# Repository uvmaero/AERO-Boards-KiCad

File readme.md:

# Readme

This repo was originally @willemcvu 's personal AERO boards repo. From 2019-20 onward it will be used by all of AERO to store boards designed for the AERO cars.

Some are finished and have been produced, tested, etc. Others have not. Up to you to figure out if a particular board might be useful for your needs.

If you do produce a board, let me know! I'd love to know what you're using it for.

Everything here is licensed under CC-BY-SA and thus is OSHWA-compliant.

# The Boards

(Often out-of-date) descriptions of what these boards do.

## BattMon

Monitors the current/voltage to/from a battery and power consumer. Includes a relay on the battery, ATMega328p, and CANBUS interface. This board has been produced and partially tested.

## CANShield
A generic Arduino Uno CANBUS shield. Once hooked up to an Uno, it is the same circuit used for all the boards with CANBUS+ATMega328p found here. Untested and unproduced.

## DC_DCBoard - Superseded by interface-board ("BigBoi")
Converts ~300VDC to ~12VDC using a DCM CHiP module from Vicor Power. Can do 400W peak, will dissapate almost 40W at that load, so it has a 19mm Vicor heatsink, model #(?can't remember).  Version 1 has clearance issues. Version 2 is an intermediate version with those issues mostly fixed. Version 3 is still be designed, and it will be the final version. None have been produced or tested, and all probably have issues (v1 and v2 have known issues, and v3 isn't finished).

## FanBoy - Superseded by interface-board ("BigBoi")
Simple 4-channel PWM fan controller with ATMega328p and CANBUS interface. Tested, works great. Should be able to do ~15A a channel, although this hasn't been tested, and is probably not recommended.

## interface-board (aka "BigBoi")
Contains all the high-voltage interface circuitry. Hosts a Vicor DC/DC converter module that generates 12V for the entire car. Also controls fans, pump, and brakelight, and includes CANBUS interface, NTC inputs, and some assorted other functionality. "standoffs-biggerbox" is the current working version. Competition-tested, working 100%.

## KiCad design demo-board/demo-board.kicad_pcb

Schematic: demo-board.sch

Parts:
C1: 0.1U; C_0603_1608Metric_Pad1.05x0.95mm_HandSolder
C2: 10U; C_0603_1608Metric_Pad1.05x0.95mm_HandSolder
D1, D2, D3, D4, D5, D6, D7, D8: WS2812B; LED_WS2812B_PLCC4_5.0x5.0mm_P3.2mm
J1: USB_B_Micro; USB_Micro-B_Molex-105017-0001
J2: Conn_02x03_Odd_Even; PinHeader_2x03_P2.54mm_Vertical
JP1, JP2, JP3, JP4, JP5, JP6, JP7, JP8: Jumper_2_Open; SolderJumper-2_P1.3mm_Open_RoundedPad1.0x1.5mm
R1: 1OK; R_0603_1608Metric_Pad1.05x0.95mm_HandSolder
U1: ATtiny85-20SU; SOIJ-8_5.3x5.3mm_P1.27mm

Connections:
+5V: C1.1, C2.1, D1.1 (VDD), D2.1 (VDD), D3.1 (VDD), D4.1 (VDD), D5.1 (VDD), D6.1 (VDD), D7.1 (VDD), D8.1 (VDD), J1.1 (VBUS), J2.2, R1.1, U1.8 (VCC)
/MISO: J2.1, U1.6 (PB1)
/MOSI: J2.4, U1.5 (AREF/PB0)
/RST: J2.5, R1.2, U1.1 (~RESET~/PB5)
/SCK: J2.3, U1.7 (PB2)
GND: C1.2, C2.2, D1.3 (VSS), D2.3 (VSS), D3.3 (VSS), D4.3 (VSS), D5.3 (VSS), D6.3 (VSS), D7.3 (VSS), D8.3 (VSS), J1.5 (GND), J1.6 (Shield), J2.6, U1.4 (GND)
unnamed: D1.2 (DOUT), D3.4 (DIN), JP1.2 (B), JP3.1 (A)
unnamed: D1.4 (DIN), JP1.1 (A), U1.2 (XTAL1/PB3)
unnamed: D2.2 (DOUT), D4.4 (DIN), JP2.2 (B), JP4.1 (A)
unnamed: D2.4 (DIN), D7.2 (DOUT), JP2.1 (A), JP7.2 (B)
unnamed: D3.2 (DOUT), D5.4 (DIN), JP3.2 (B), JP5.1 (A)
unnamed: D4.2 (DOUT), D6.4 (DIN), JP4.2 (B), JP6.1 (A)
unnamed: D5.2 (DOUT), D7.4 (DIN), JP5.2 (B), JP7.1 (A)
unnamed: D6.2 (DOUT), D8.4 (DIN), JP6.2 (B), JP8.1 (A)
unnamed: D8.2 (DOUT), JP8.2 (B)

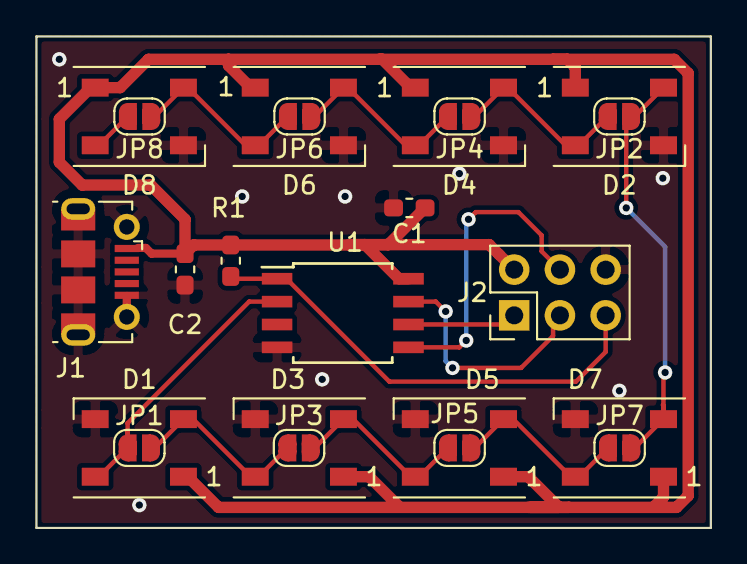
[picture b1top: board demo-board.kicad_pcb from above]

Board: 2 copper layers, 37.5 x 27.3 mm, 22 parts (0 on the bottom side), 15 nets.

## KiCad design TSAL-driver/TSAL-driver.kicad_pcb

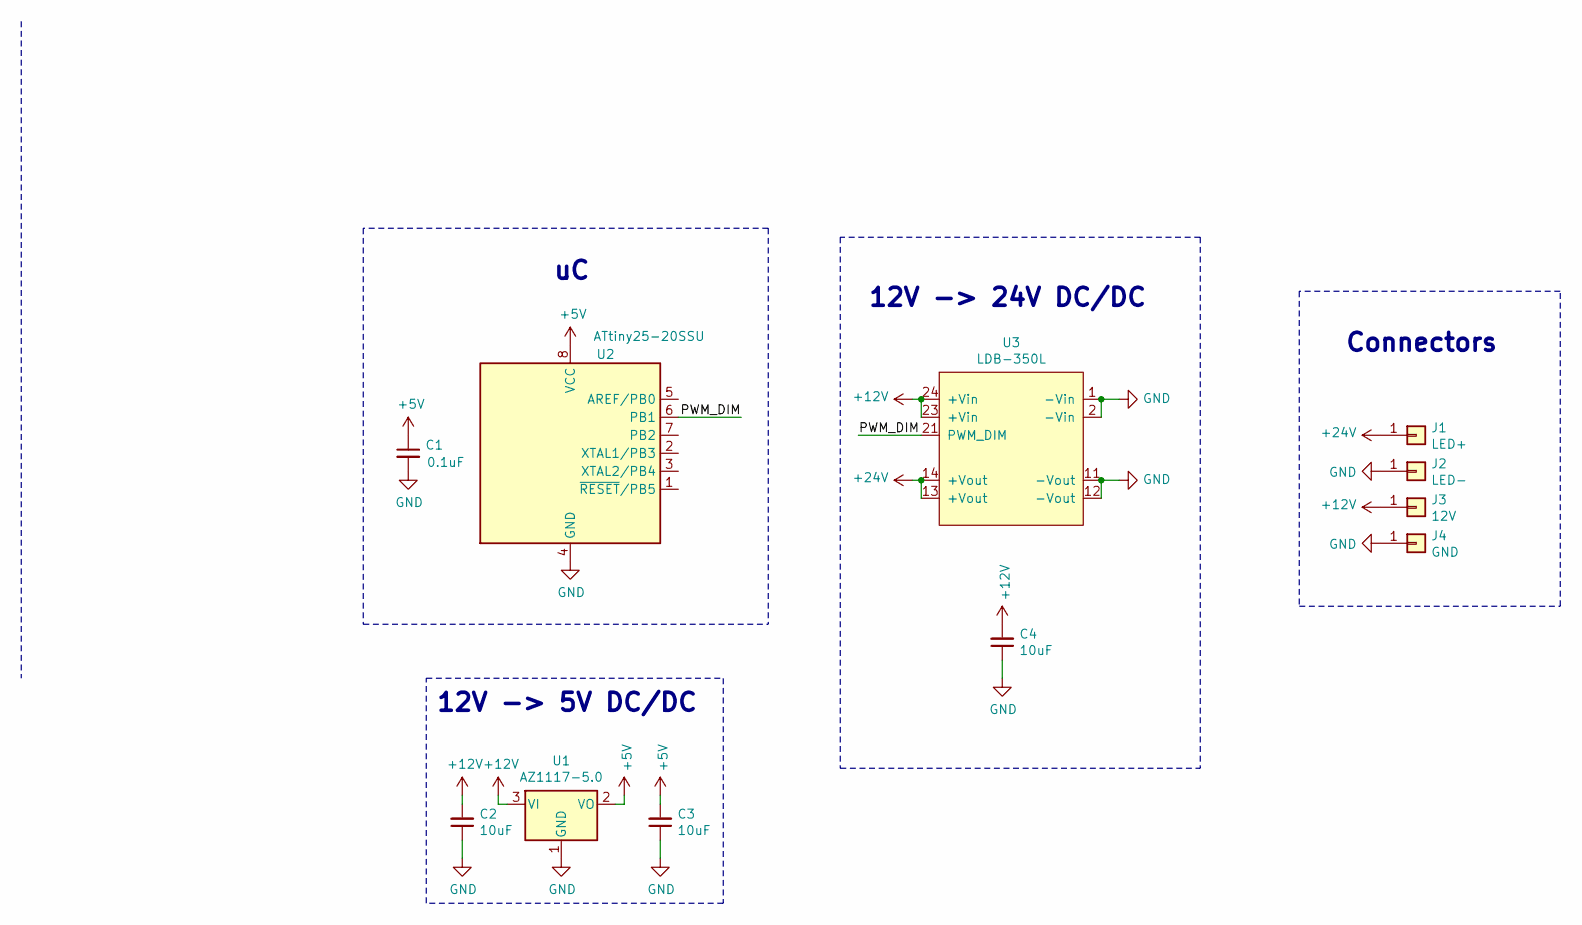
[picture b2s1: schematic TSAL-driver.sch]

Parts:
C1: 0.1uF; C_0603_1608Metric
C2, C3, C4: 10uF; C_0603_1608Metric
J1: LED+; TE_1217861-1
J2: LED-; TE_1217861-1
J3: 12V; TE_1217861-1
J4: GND; TE_1217861-1
U1: AZ1117-5.0; SOT-223-3_TabPin2
U2: ATtiny25-20SSU; SOIC-8_3.9x4.9mm_P1.27mm
U3: LDB-350L; LDB-_L

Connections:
+5V: C1.1, C3.2, U1.2 (VO), U2.8 (VCC)
+12V: C2.2, C4.2, J3.1, U1.3 (VI), U3.23 (+Vin), U3.24 (+Vin)
+24V: J1.1, U3.13 (+Vout), U3.14 (+Vout)
/PWM_DIM: U2.6 (PB1), U3.21 (PWM_DIM)
GND: C1.2, C2.1, C3.1, C4.1, J2.1, J4.1, U1.1 (GND), U2.4 (GND), U3.1 (-Vin), U3.2 (-Vin), U3.11 (-Vout), U3.12 (-Vout)

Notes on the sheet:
12V -> 24V DC/DC
Connectors
12V -> 5V DC/DC

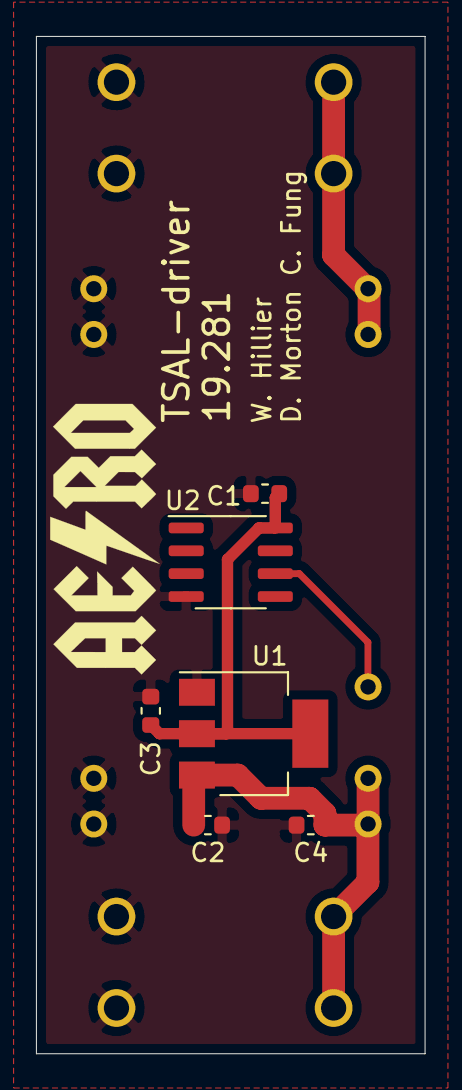
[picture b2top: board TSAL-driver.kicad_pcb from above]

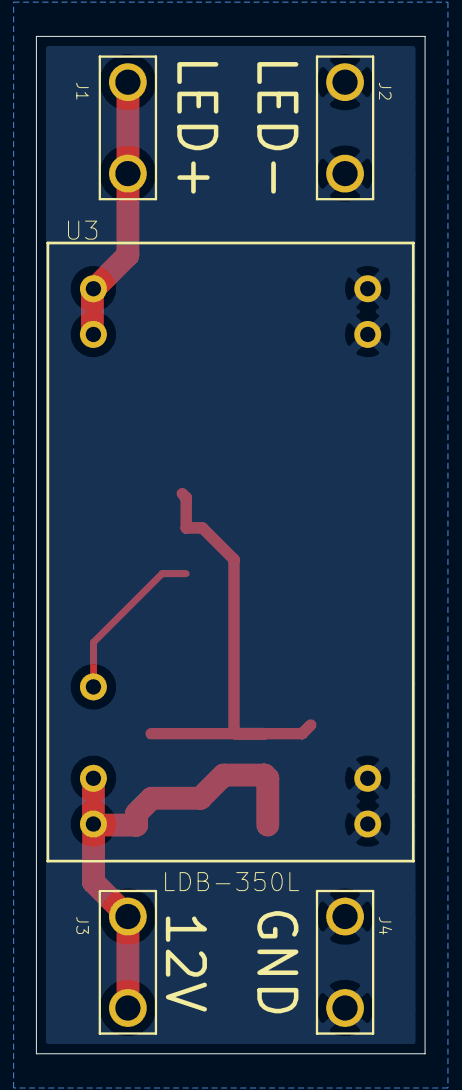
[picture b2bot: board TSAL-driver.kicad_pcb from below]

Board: 2 copper layers, 21.6 x 56.5 mm, 11 parts (5 on the bottom side), 5 nets.

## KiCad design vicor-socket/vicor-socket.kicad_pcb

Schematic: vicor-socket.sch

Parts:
J1: Interface; PinHeader_1x03_P2.54mm_Vertical
J2: HV+; MountingHole_3.2mm_M3_Pad_Via
J3: HV-; MountingHole_3.2mm_M3_Pad_Via
J4: 12V+; MountingHole_3.2mm_M3_Pad_Via
J5: 12V-; MountingHole_3.2mm_M3_Pad_Via
U1: DCM4623TD2J13D0T70-AEROParts; DCM4623TD2J13D0T70_w_landpattern

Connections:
unnamed: J1.1, U1.4 (FT)
unnamed: J1.2, U1.3 (EN)
unnamed: J1.3, U1.2 (TR)
unnamed: J2.1, U1.1 (+IN)
unnamed: J3.1, U1.5 (-IN)
unnamed: J4.1, U1.7 (+OUT), U1.9 (+OUT)
unnamed: J5.1, U1.6 (-OUT), U1.8 (-OUT)

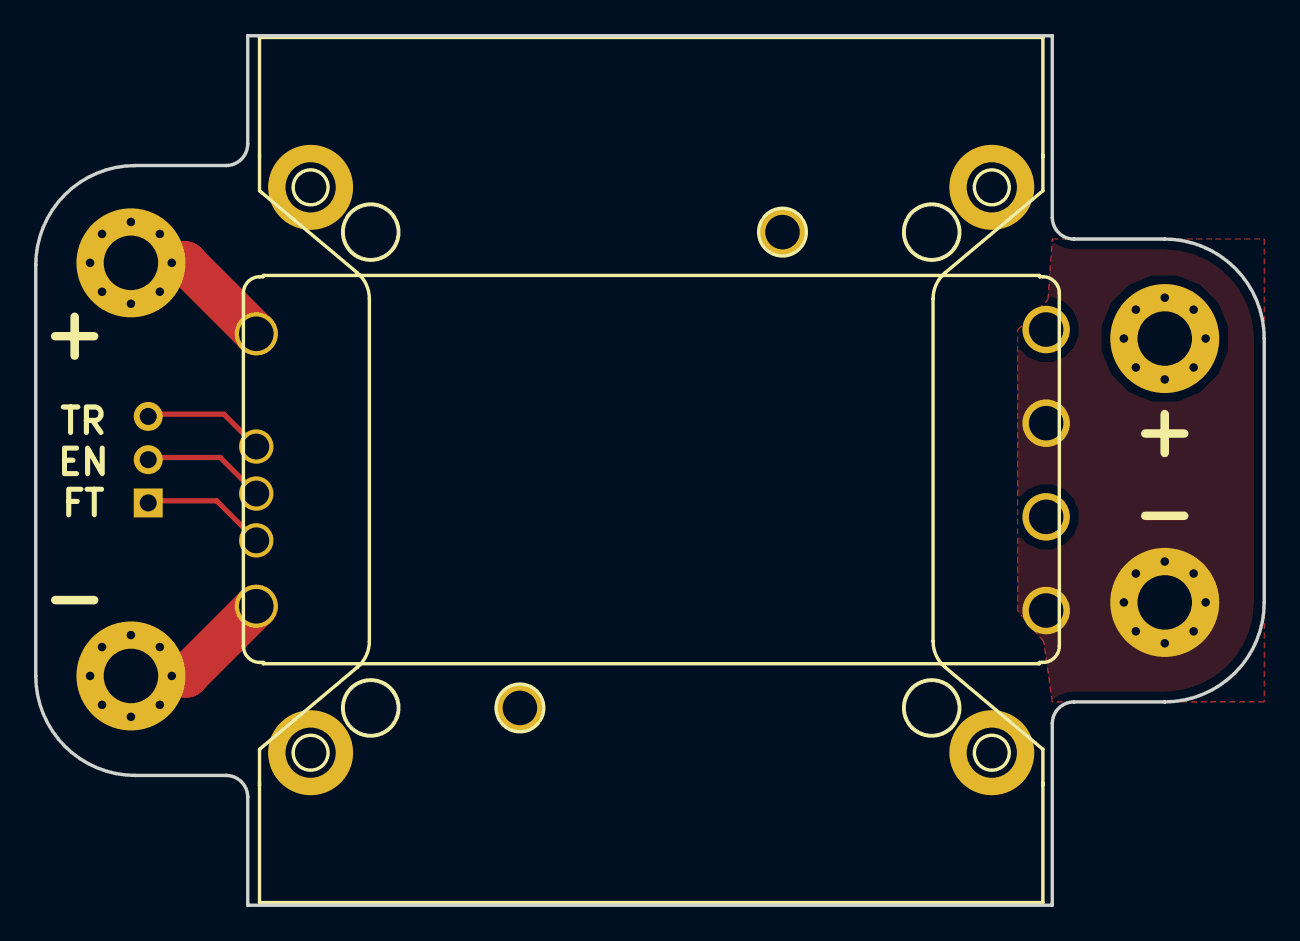
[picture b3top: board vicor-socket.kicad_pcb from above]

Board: 2 copper layers, 72.1 x 51.1 mm, 6 parts (1 on the bottom side), 7 nets.

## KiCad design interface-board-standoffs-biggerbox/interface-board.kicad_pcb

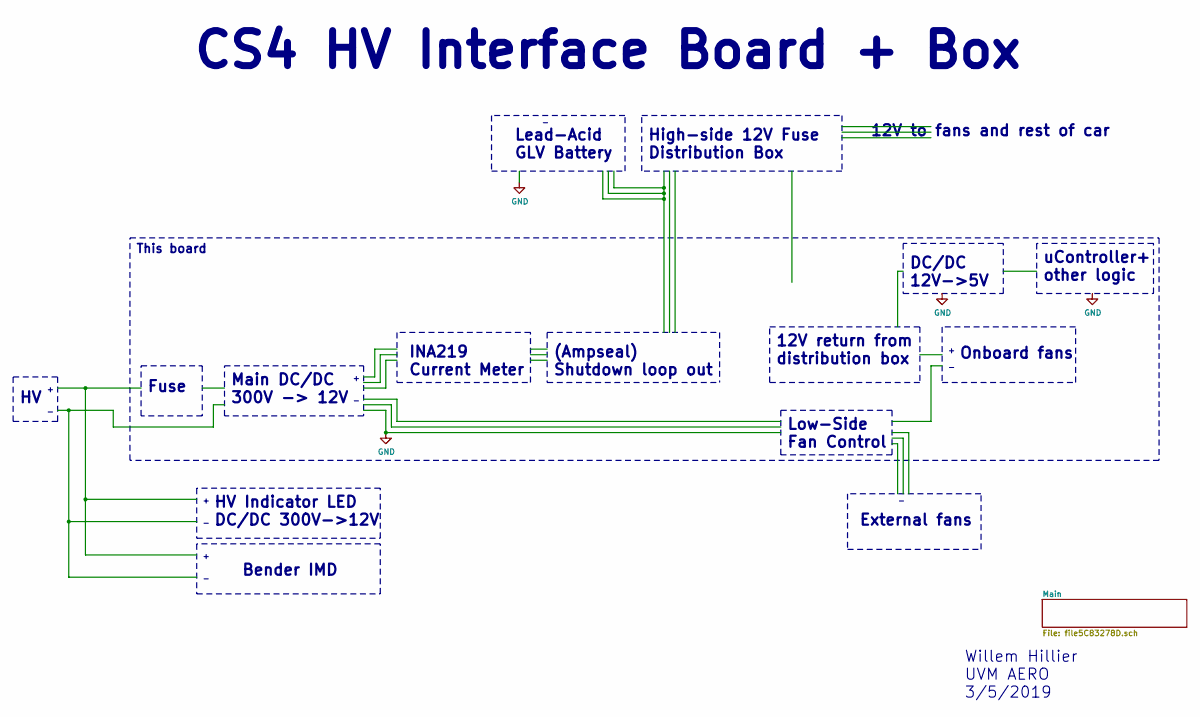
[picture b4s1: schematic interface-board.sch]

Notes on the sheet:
CS4 HV Interface Board + Box
Main DC/DC 300V -> 12V
HV Indicator LED DC/DC 300V->12V
INA219 Current Meter
(Ampseal) Shutdown loop out
Fuse
DC/DC 12V->5V
Low-Side Fan Control
High-side 12V Fuse Distribution Box
12V return from distribution box
uController+ other logic
Onboard fans
This board
External fans
12V to fans and rest of car
Willem Hillier UVM AERO 3/5/2019
Bender IMD
Lead-Acid GLV Battery

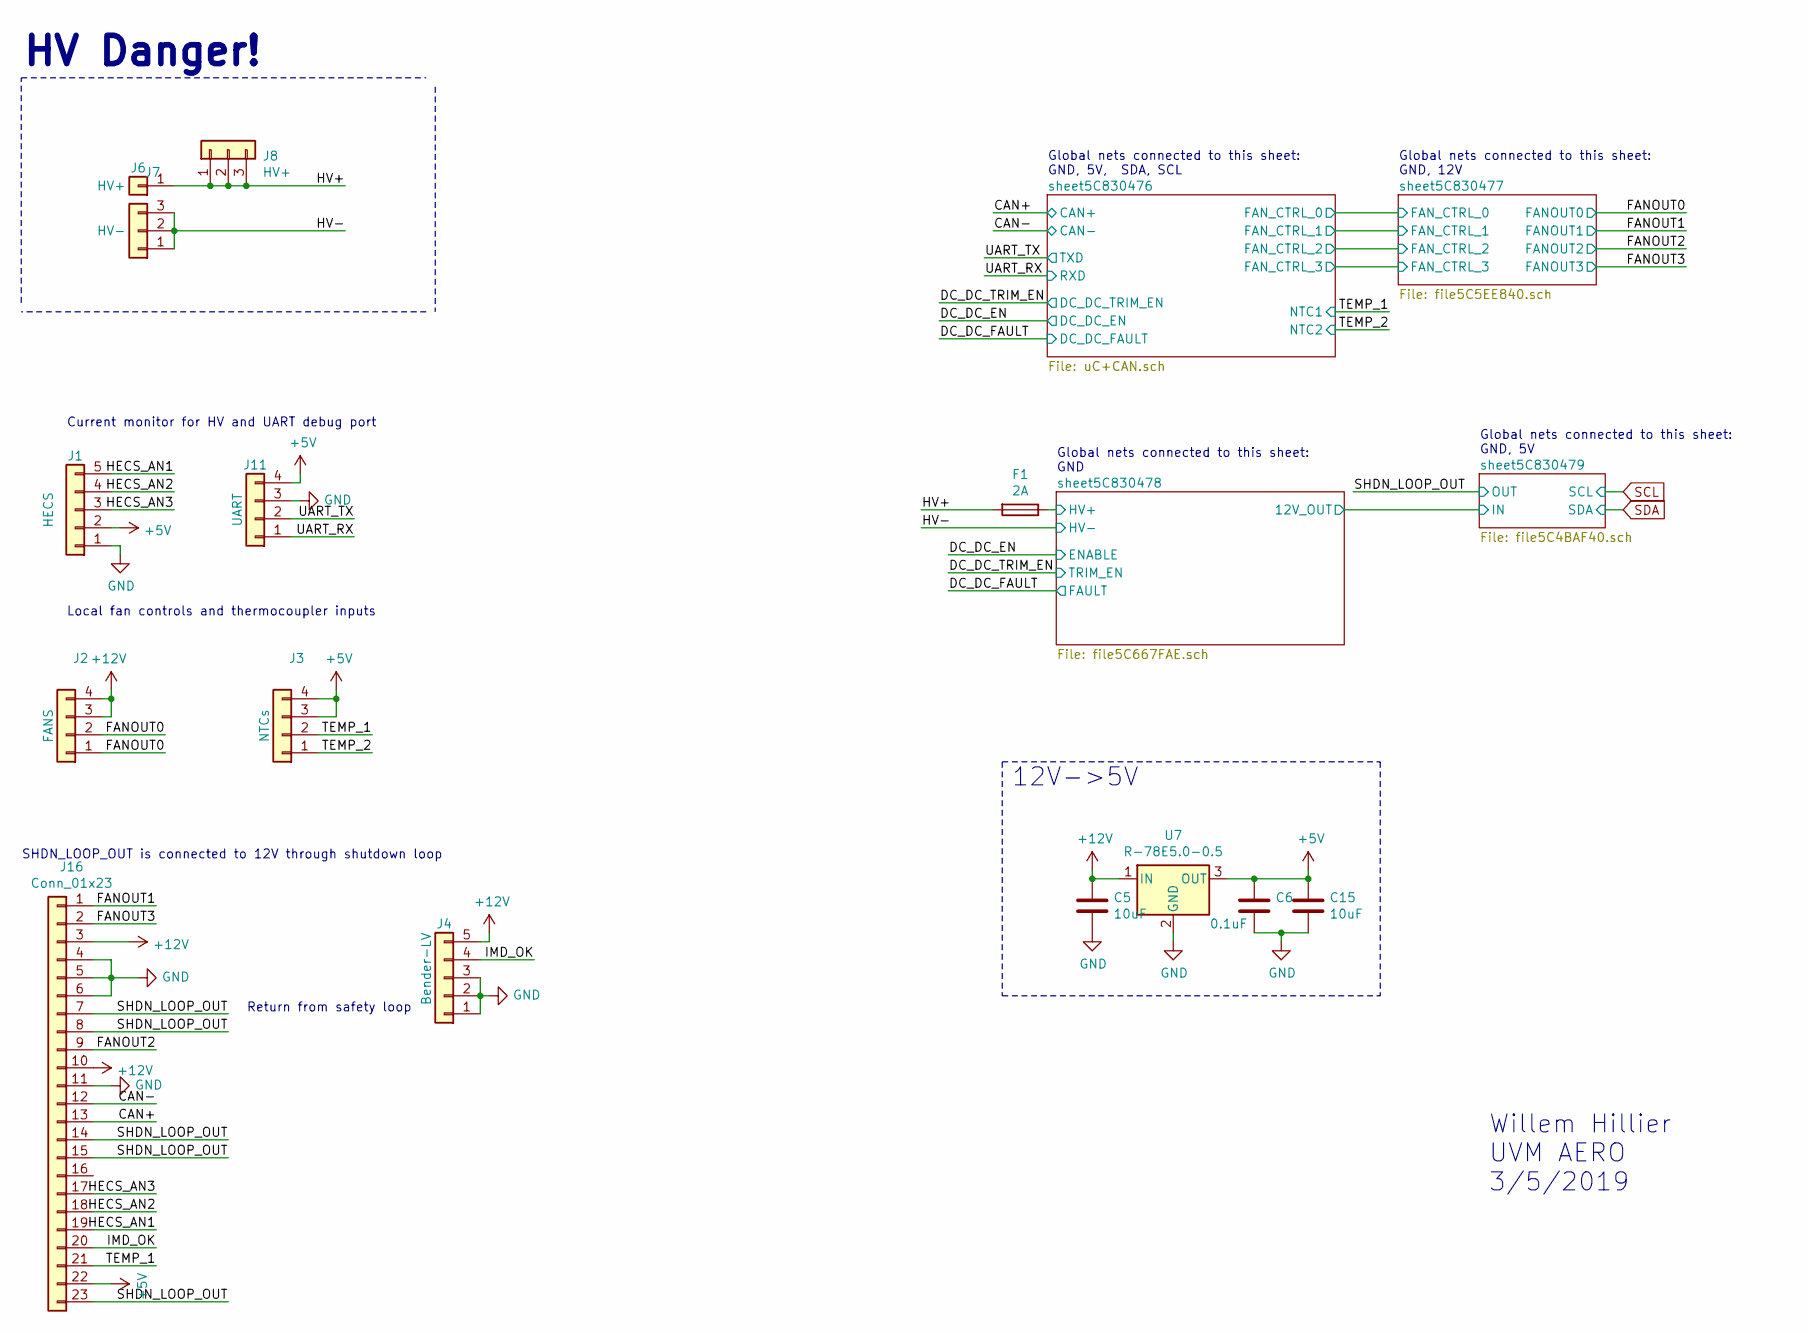
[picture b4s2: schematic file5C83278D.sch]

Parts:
C5, C15: 10uF; C_0603_1608Metric
C6: 0.1uF; C_0603_1608Metric
F1: 2A; Fuseholder_Cylinder-5x20mm_Schurter_0031_8201_Horizontal_Op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
J1: HECS; Molex_KK-254_AE-6410-05A_1x05_P2.54mm_Vertical
J2: FANS; JST_PH_B4B-PH-K_1x04_P2.00mm_Vertical
J3: NTCs; JST_PH_B4B-PH-K_1x04_P2.00mm_Vertical
J4: Bender-LV; Molex_KK-254_AE-6410-05A_1x05_P2.54mm_Vertical
J6: HV+; MountingHole_4.3mm_M4_Pad_Via
J7: HV-; TE_MATE-N-LOK_1-770870-x_1x03_P4.14mm_Vertical
J8: HV+; TE_MATE-N-LOK_1-770870-x_1x03_P4.14mm_Vertical
J11: UART; PinSocket_1x04_P2.54mm_Vertical
J16: Conn_01x23; TE_1-776087-1
U7: R-78E5.0-0.5; Converter_DCDC_RECOM_R-78E-0.5_THT

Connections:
+5V: C6.1, C15.1, J1.2, J3.3, J3.4, J11.4, J16.22, U7.3 (OUT); also elsewhere on the board
+12V: C5.1, J2.3, J2.4, J4.5, J16.3, J16.10, U7.1 (IN); also elsewhere on the board
/Main/CAN+: J16.13; also elsewhere on the board
/Main/CAN-: J16.12; also elsewhere on the board
/Main/FANOUT0: J2.1, J2.2; also elsewhere on the board
/Main/FANOUT1: J16.1; also elsewhere on the board
/Main/FANOUT2: J16.9; also elsewhere on the board
/Main/FANOUT3: J16.2; also elsewhere on the board
/Main/HECS_AN1: J1.5, J16.19
/Main/HECS_AN2: J1.4, J16.18
/Main/HECS_AN3: J1.3, J16.17
/Main/HV+: F1.2, J6.1, J8.1, J8.2, J8.3
/Main/HV-: J7.1, J7.2, J7.3; also elsewhere on the board
/Main/IMD_OK: J4.4, J16.20
/Main/SHDN_LOOP_OUT: J16.7, J16.8, J16.14, J16.15, J16.23; also elsewhere on the board
/Main/TEMP_1: J3.2, J16.21; also elsewhere on the board
/Main/TEMP_2: J3.1; also elsewhere on the board
/Main/UART_RX: J11.1; also elsewhere on the board
/Main/UART_TX: J11.2; also elsewhere on the board
/Main/sheet5C830478/HV+: F1.1; also elsewhere on the board
GND: C5.2, C6.2, C15.2, J1.1, J4.1, J4.2, J4.3, J11.3, J16.4, J16.5, J16.6, J16.11, U7.2 (GND); also elsewhere on the board

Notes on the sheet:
Global nets connected to this sheet: GND, 5V, SDA, SCL
Global nets connected to this sheet: GND, 12V
Global nets connected to this sheet: GND
Global nets connected to this sheet: GND, 5V
HV Danger!
Return from safety loop
SHDN_LOOP_OUT is connected to 12V through shutdown loop
Local fan controls and thermocoupler inputs
Current monitor for HV and UART debug port
12V->5V
Willem Hillier UVM AERO 3/5/2019

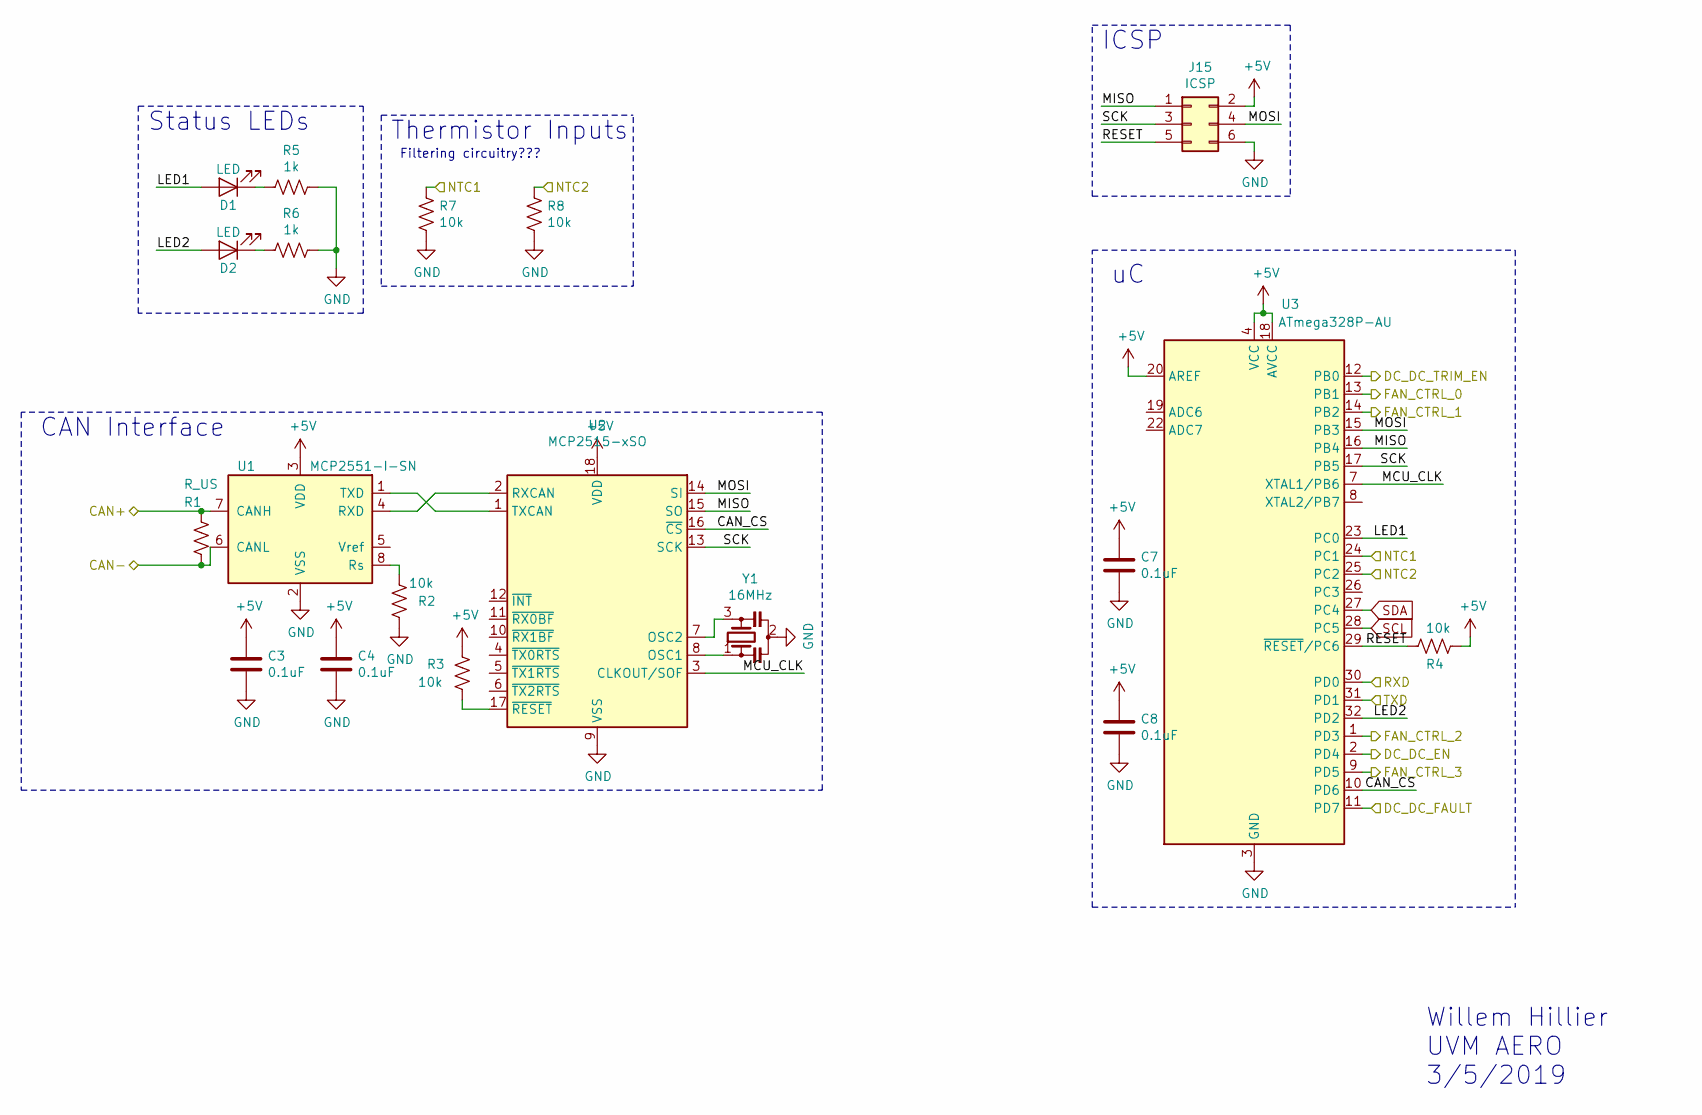
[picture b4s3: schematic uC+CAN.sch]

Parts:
C3, C4, C7, C8: 0.1uF; C_0603_1608Metric
D1, D2: LED; LED_0603_1608Metric
J15: ICSP; PinSocket_2x03_P2.54mm_Vertical
R1: R_US; R_0603_1608Metric
R2, R3, R4, R7, R8: 10k; R_0603_1608Metric
R5, R6: 1k; R_0603_1608Metric
U1: MCP2551-I-SN; SOIC-8_3.9x4.9mm_P1.27mm
U2: MCP2515-xSO; SOIC-18W_7.5x11.6mm_P1.27mm
U3: ATmega328P-AU; TQFP-32_7x7mm_P0.8mm
Y1: 16MHz; Resonator_SMD_muRata_CSTxExxV-3Pin_3.0x1.1mm

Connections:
+5V: C3.1, C4.1, C7.1, C8.1, J15.2, R3.1, R4.1, U1.3 (VDD), U2.18 (VDD), U3.4 (VCC), U3.6 (VCC), U3.18 (AVCC), U3.20 (AREF); also elsewhere on the board
/Main/CAN+: R1.1, U1.7 (CANH); also elsewhere on the board
/Main/CAN-: R1.2, U1.6 (CANL); also elsewhere on the board
/Main/DC_DC_EN: U3.2 (PD4); also elsewhere on the board
/Main/DC_DC_FAULT: U3.11 (PD7); also elsewhere on the board
/Main/TEMP_1: R7.2, U3.24 (PC1); also elsewhere on the board
/Main/TEMP_2: R8.2, U3.25 (PC2); also elsewhere on the board
/Main/UART_RX: U3.30 (PD0); also elsewhere on the board
/Main/UART_TX: U3.31 (PD1); also elsewhere on the board
/Main/sheet5C830476/CAN_CS: U2.16 (~CS), U3.10 (PD6)
/Main/sheet5C830476/FAN_CTRL_0: U3.13 (PB1); also elsewhere on the board
/Main/sheet5C830476/FAN_CTRL_1: U3.14 (PB2); also elsewhere on the board
/Main/sheet5C830476/FAN_CTRL_2: U3.1 (PD3); also elsewhere on the board
/Main/sheet5C830476/FAN_CTRL_3: U3.9 (PD5); also elsewhere on the board
/Main/sheet5C830476/LED1: D1.2 (A), U3.23 (PC0)
/Main/sheet5C830476/LED2: D2.2 (A), U3.32 (PD2)
/Main/sheet5C830476/MCU_CLK: U2.3 (CLKOUT/SOF), U3.7 (XTAL1/PB6)
/Main/sheet5C830476/MISO: J15.1, U2.15 (SO), U3.16 (PB4)
/Main/sheet5C830476/MOSI: J15.4, U2.14 (SI), U3.15 (PB3)
/Main/sheet5C830476/RESET: J15.5, R4.2, U3.29 (~RESET~/PC6)
/Main/sheet5C830476/SCK: J15.3, U2.13 (SCK), U3.17 (PB5)
GND: C3.2, C4.2, C7.2, C8.2, J15.6, R2.2, R5.1, R6.1, R7.1, R8.1, U1.2 (VSS), U2.9 (VSS), U3.3 (GND), U3.5 (GND), U3.21 (GND), Y1.2; also elsewhere on the board
unnamed: D1.1 (K), R5.2
unnamed: D2.1 (K), R6.2
unnamed: R2.1, U1.8 (Rs)
unnamed: R3.2, U2.17 (~RESET)
unnamed: U1.1 (TXD), U2.1 (TXCAN)
unnamed: U1.4 (RXD), U2.2 (RXCAN)
unnamed: U2.7 (OSC2), Y1.3
unnamed: U2.8 (OSC1), Y1.1
SCL: U3.28 (PC5); also elsewhere on the board
SDA: U3.27 (PC4); also elsewhere on the board

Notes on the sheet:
CAN Interface
ICSP
Status LEDs
Thermistor Inputs
Filtering circuitry???
Willem Hillier UVM AERO 3/5/2019

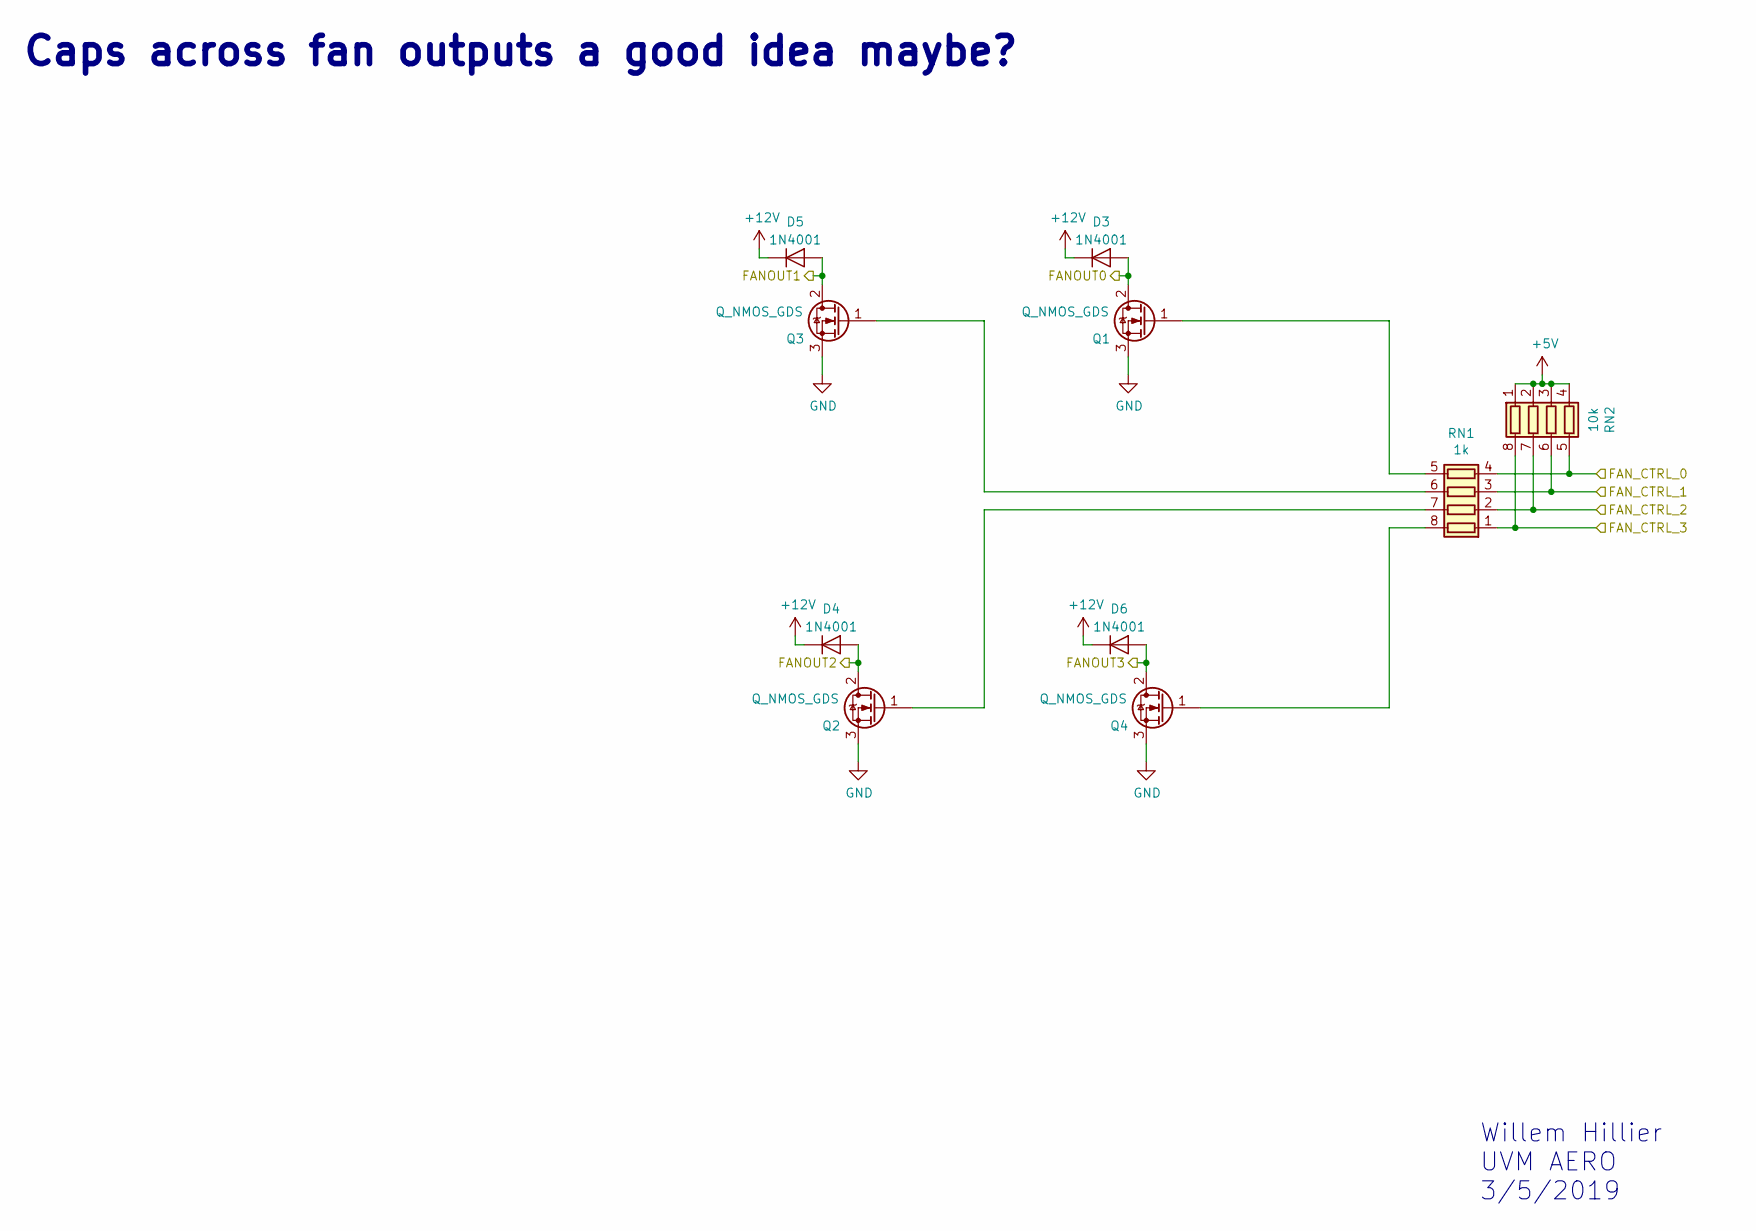
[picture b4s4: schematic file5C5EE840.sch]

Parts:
D3, D4, D5, D6: 1N4001; D_DO-41_SOD81_P10.16mm_Horizontal
Q1, Q2, Q3, Q4: Q_NMOS_GDS; TO-252-2
RN1: 1k; R_Array_Convex_4x0603
RN2: 10k; R_Array_Convex_4x0603

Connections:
+5V: RN2.1 (R1.1), RN2.2 (R2.1), RN2.3 (R3.1), RN2.4 (R4.1); also elsewhere on the board
+12V: D3.1 (K), D4.1 (K), D5.1 (K), D6.1 (K); also elsewhere on the board
/Main/FANOUT0: D3.2 (A), Q1.2 (D); also elsewhere on the board
/Main/FANOUT1: D5.2 (A), Q3.2 (D); also elsewhere on the board
/Main/FANOUT2: D4.2 (A), Q2.2 (D); also elsewhere on the board
/Main/FANOUT3: D6.2 (A), Q4.2 (D); also elsewhere on the board
/Main/sheet5C830476/FAN_CTRL_0: RN1.4 (R4.1), RN2.5 (R4.2); also elsewhere on the board
/Main/sheet5C830476/FAN_CTRL_1: RN1.3 (R3.1), RN2.6 (R3.2); also elsewhere on the board
/Main/sheet5C830476/FAN_CTRL_2: RN1.2 (R2.1), RN2.7 (R2.2); also elsewhere on the board
/Main/sheet5C830476/FAN_CTRL_3: RN1.1 (R1.1), RN2.8 (R1.2); also elsewhere on the board
GND: Q1.3 (S), Q2.3 (S), Q3.3 (S), Q4.3 (S); also elsewhere on the board
unnamed: Q1.1 (G), RN1.5 (R4.2)
unnamed: Q2.1 (G), RN1.7 (R2.2)
unnamed: Q3.1 (G), RN1.6 (R3.2)
unnamed: Q4.1 (G), RN1.8 (R1.2)

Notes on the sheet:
Caps across fan outputs a good idea maybe?
Willem Hillier UVM AERO 3/5/2019

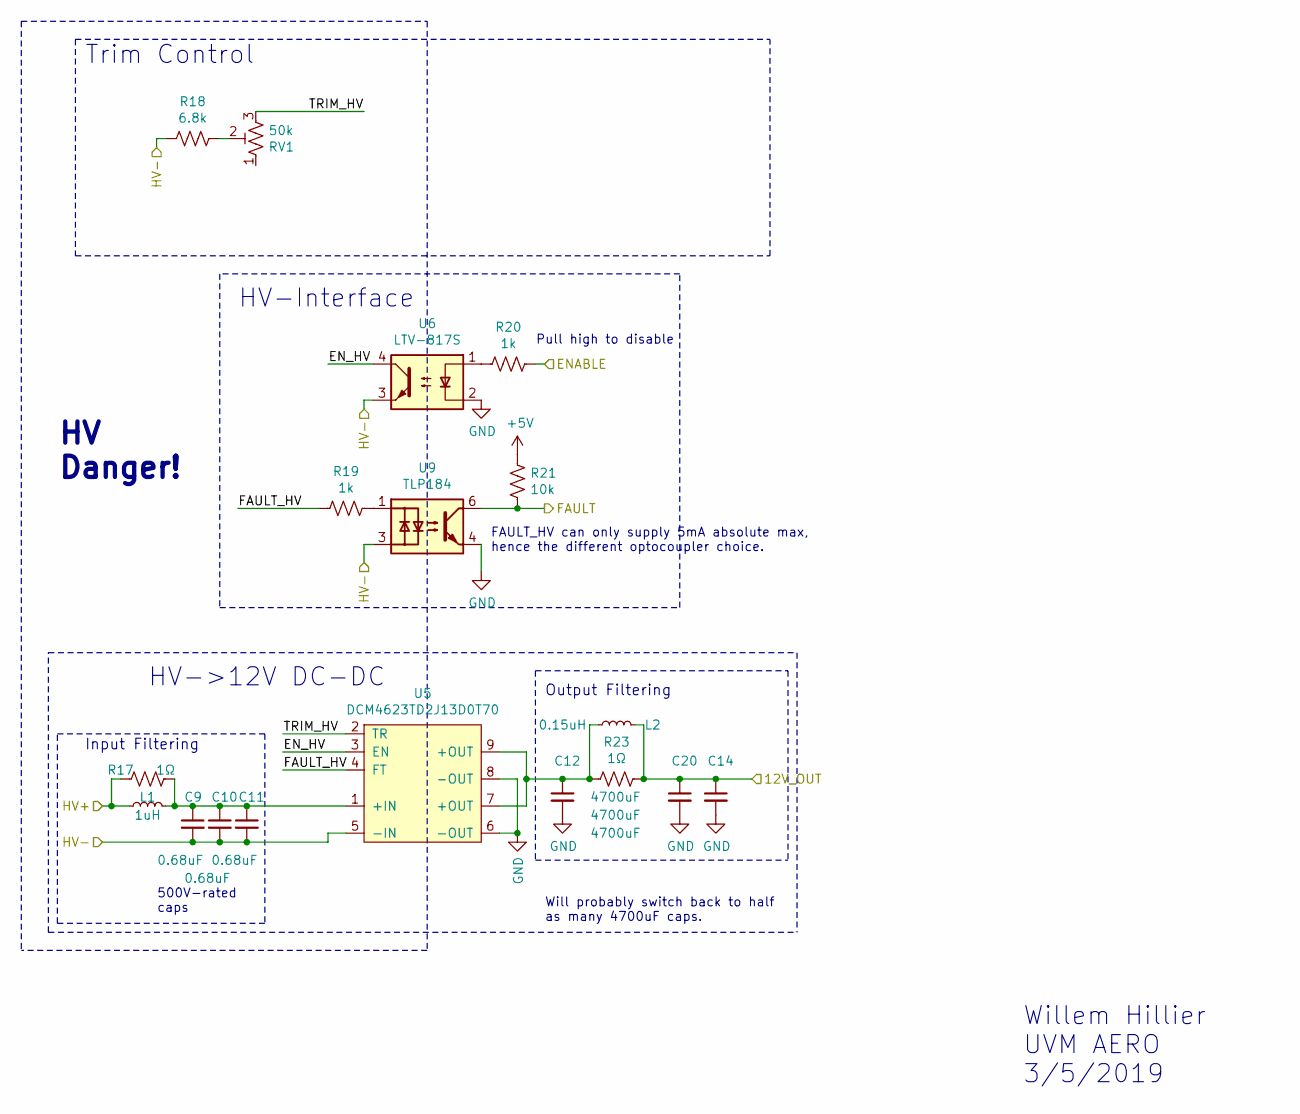
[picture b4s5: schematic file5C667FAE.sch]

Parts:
C9, C10, C11: 0.68uF; C_Rect_L18.0mm_W8.0mm_P15.00mm_FKS3_FKP3
C12, C14, C20: 4700uF; CP_Radial_D18.0mm_P7.50mm
L1: 1uH; Murata_DFE252012P_Inductor
L2: 0.15uH; PA2607
R17, R23: 1Ω; R_2512_6332Metric
R18: 6.8k; R_0603_1608Metric
R19, R20: 1k; R_0603_1608Metric
R21: 10k; R_0603_1608Metric
RV1: 50k; TC33X-503ECT-ND
U5: DCM4623TD2J13D0T70; vicor-socket-no-cutouts
U6: LTV-817S; SMDIP-4_W9.53mm
U9: TLP184; TLP182

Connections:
+5V: R21.2; also elsewhere on the board
/Main/DC_DC_EN: R20.1; also elsewhere on the board
/Main/DC_DC_FAULT: R21.1, U9.6; also elsewhere on the board
/Main/HV-: C9.2, C10.2, C11.2, R18.2, U5.5 (-IN), U6.3, U9.3; also elsewhere on the board
/Main/sheet5C830478/12V_OUT: C14.1, C20.1, L2.2, R23.1; also elsewhere on the board
/Main/sheet5C830478/EN_HV: U5.3 (EN), U6.4
/Main/sheet5C830478/FAULT_HV: R19.2, U5.4 (FT)
/Main/sheet5C830478/HV+: L1.1, R17.2; also elsewhere on the board
/Main/sheet5C830478/TRIM_HV: RV1.3, U5.2 (TR)
GND: C12.2, C14.2, C20.2, U5.6 (-OUT), U5.8 (-OUT), U6.2, U9.4; also elsewhere on the board
unnamed 39: C12.1, L2.1, R23.2, U5.7 (+OUT), U5.9 (+OUT); also elsewhere on the board
unnamed: C9.1, C10.1, C11.1, L1.2, R17.1, U5.1 (+IN)
unnamed: R18.1, RV1.2
unnamed: R19.1, U9.1
unnamed: R20.2, U6.1

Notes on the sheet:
500V-rated caps
Input Filtering
Trim Control
Pull high to disable
HV->12V DC-DC
HV-Interface
HV Danger!
Output Filtering
FAULT_HV can only supply 5mA absolute max, hence the different optocoupler choice.
Will probably switch back to half as many 4700uF caps.
Willem Hillier UVM AERO 3/5/2019

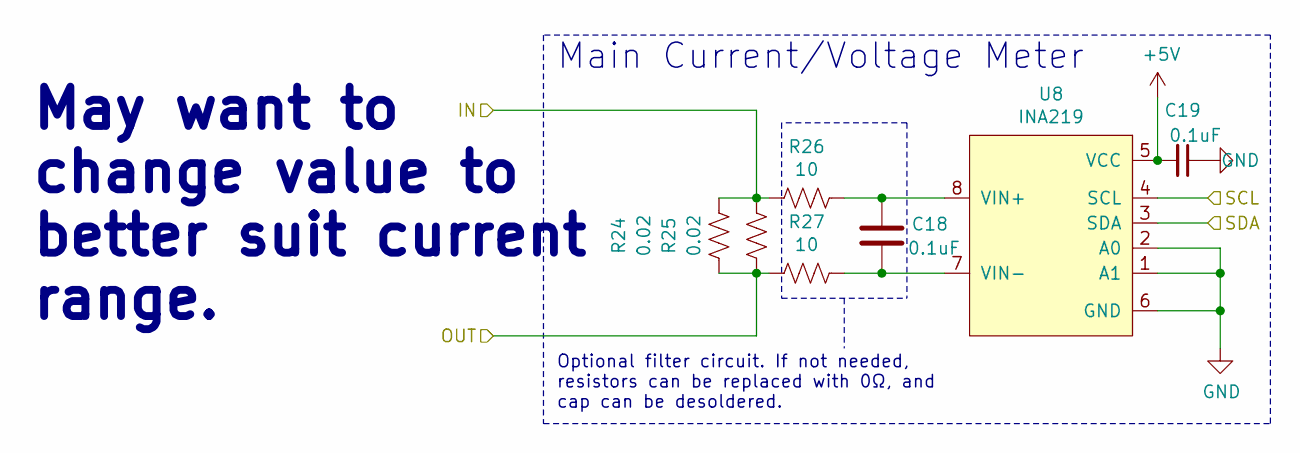
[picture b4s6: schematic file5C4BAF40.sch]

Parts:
C18, C19: 0.1uF; C_0603_1608Metric
R24, R25: 0.02; R_2512_6332Metric
R26, R27: 10; R_0603_1608Metric
U8: INA219; SOIC-8_3.9x4.9mm_P1.27mm

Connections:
+5V: C19.2, U8.5 (VCC); also elsewhere on the board
/Main/SHDN_LOOP_OUT: R24.1, R25.1, R27.2; also elsewhere on the board
/Main/sheet5C830478/12V_OUT: R24.2, R25.2, R26.2; also elsewhere on the board
GND: C19.1, U8.1 (A1), U8.2 (A0), U8.6 (GND); also elsewhere on the board
unnamed: C18.1, R26.1, U8.8 (VIN+)
unnamed: C18.2, R27.1, U8.7 (VIN-)
SCL: U8.4 (SCL); also elsewhere on the board
SDA: U8.3 (SDA); also elsewhere on the board

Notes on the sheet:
May want to change value to better suit current range.
Main Current/Voltage Meter
Optional filter circuit. If not needed, resistors can be replaced with 0Ω, and cap can be desoldered.
